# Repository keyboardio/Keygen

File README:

Setting up:

* Install perl modules
* Check out git submodule

Perl Dependencies:

JSON::XS
Moose

Non-perl Dependencies:

This tool currently builds KiCad 6.0 projects. That's not strictly necessary. If you need us to back down to 5.1, please say so.

There's a git submodule of 'kicad', which includes the keyboardio kicad footprints. Pull requests over there are welcome.

Usage:

perl layout.pl --usb=c --project=104-key --layout=kle-layouts/104.json 
cd 104-key
kicad 104-key.pro

Notes:

It currently generates schematics and layouts assuming a ATMega32U4. The schematic has sheets for three different ways to wire things up: components-on-pcb, teensy 2.0++, arduino-micro.
I know the pro micro is more popular in Japan and I'm happy to have that added as an option.
It'd just need another schematic sheet in the template project and a footprint for adding it to the pcb.
led support is a boolean option. Right now, LEDs are designed as dumb rgb pixels + an issi controller.
the logic parts of the PCB don't get placed or connected to the switch and led matrix automatically. That's a much harder wiring problem.
Instead, I hand-drew layouts for those and place them off the side of the PCB for you to drag into place and wire up.
I have produced two PCBs based on earlier versions of this tool with some manual rework. They did -work-. But results are not guaranteed.

-Jesse
jesse@keyboard.io

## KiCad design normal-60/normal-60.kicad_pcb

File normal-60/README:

A test/example of a normalish 60% generated with this tooling

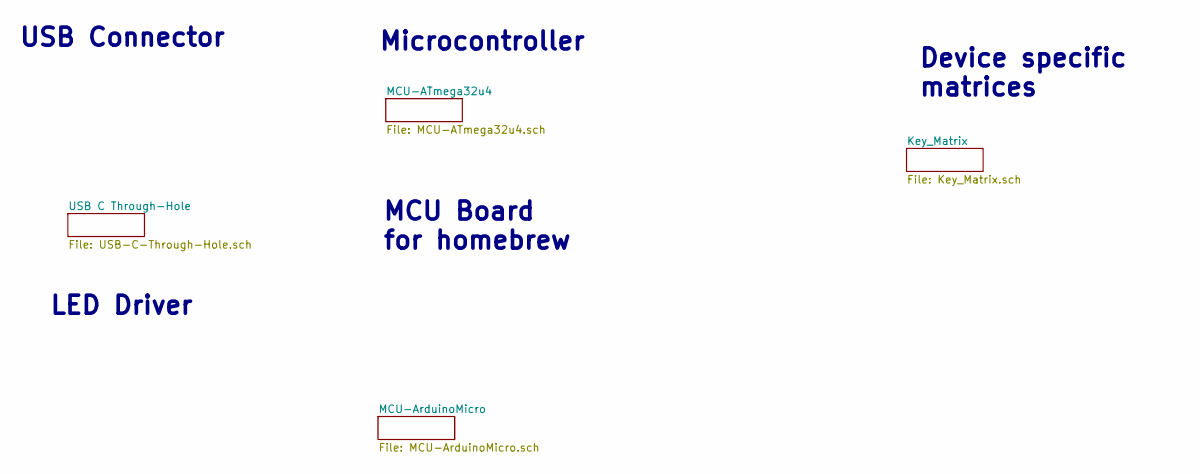
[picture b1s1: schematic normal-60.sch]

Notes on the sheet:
Device specific matrices
USB Connector
LED Driver
Microcontroller
MCU Board for homebrew

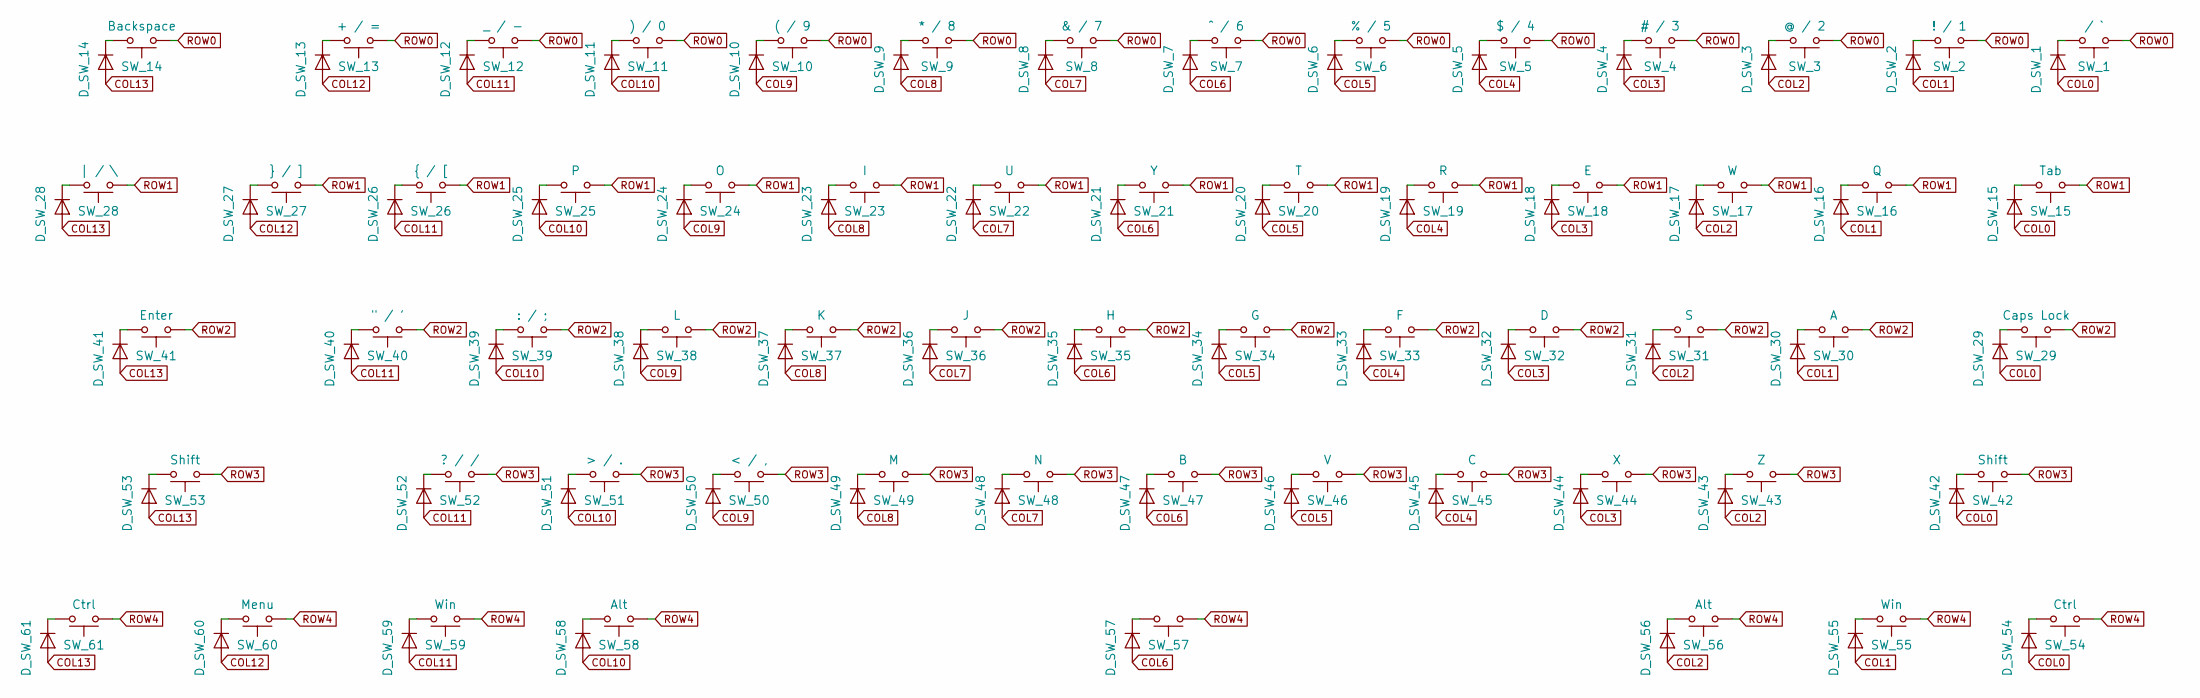
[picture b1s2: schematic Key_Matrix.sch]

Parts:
D_SW_1, D_SW_2, D_SW_3, D_SW_4, D_SW_5, D_SW_6, D_SW_7, D_SW_8, D_SW_9, D_SW_10, D_SW_11, D_SW_12, D_SW_13, D_SW_14, D_SW_15, D_SW_16, D_SW_17, D_SW_18, D_SW_19, D_SW_20, D_SW_21, D_SW_22, D_SW_23, D_SW_24, D_SW_25, D_SW_26, D_SW_27, D_SW_28, D_SW_29, D_SW_30, D_SW_31, D_SW_32, D_SW_33, D_SW_34, D_SW_35, D_SW_36, D_SW_37, D_SW_38, D_SW_39, D_SW_40, D_SW_41, D_SW_42, D_SW_43, D_SW_44, D_SW_45, D_SW_46, D_SW_47, D_SW_48, D_SW_49, D_SW_50, D_SW_51, D_SW_52, D_SW_53, D_SW_54, D_SW_55, D_SW_56, D_SW_57, D_SW_58, D_SW_59, D_SW_60, D_SW_61: 1N4148; D_SOD-123
SW_1: ~ / `; MX-KailhClip-1.00u
SW_2: ! / 1; MX-KailhClip-1.00u
SW_3: @ / 2; MX-KailhClip-1.00u
SW_4: # / 3; MX-KailhClip-1.00u
SW_5: $ / 4; MX-KailhClip-1.00u
SW_6: % / 5; MX-KailhClip-1.00u
SW_7: ^ / 6; MX-KailhClip-1.00u
SW_8: & / 7; MX-KailhClip-1.00u
SW_9: * / 8; MX-KailhClip-1.00u
SW_10: ( / 9; MX-KailhClip-1.00u
SW_11: ) / 0; MX-KailhClip-1.00u
SW_12: _ / -; MX-KailhClip-1.00u
SW_13: + / =; MX-KailhClip-1.00u
SW_14: Backspace; MX-KailhClip-1.00u
SW_15: Tab; MX-KailhClip-1.00u
SW_16: Q; MX-KailhClip-1.00u
SW_17: W; MX-KailhClip-1.00u
SW_18: E; MX-KailhClip-1.00u
SW_19: R; MX-KailhClip-1.00u
SW_20: T; MX-KailhClip-1.00u
SW_21: Y; MX-KailhClip-1.00u
SW_22: U; MX-KailhClip-1.00u
SW_23: I; MX-KailhClip-1.00u
SW_24: O; MX-KailhClip-1.00u
SW_25: P; MX-KailhClip-1.00u
SW_26: { / [; MX-KailhClip-1.00u
SW_27: } / ]; MX-KailhClip-1.00u
SW_28: | / \\; MX-KailhClip-1.00u
SW_29: Caps Lock; MX-KailhClip-1.00u
SW_30: A; MX-KailhClip-1.00u
SW_31: S; MX-KailhClip-1.00u
SW_32: D; MX-KailhClip-1.00u
SW_33: F; MX-KailhClip-1.00u
SW_34: G; MX-KailhClip-1.00u
SW_35: H; MX-KailhClip-1.00u
SW_36: J; MX-KailhClip-1.00u
SW_37: K; MX-KailhClip-1.00u
SW_38: L; MX-KailhClip-1.00u
SW_39: : / ;; MX-KailhClip-1.00u
SW_40: \" / '; MX-KailhClip-1.00u
SW_41: Enter; MX-KailhClip-1.00u
SW_42, SW_53: Shift; MX-KailhClip-1.00u
SW_43: Z; MX-KailhClip-1.00u
SW_44: X; MX-KailhClip-1.00u
SW_45: C; MX-KailhClip-1.00u
SW_46: V; MX-KailhClip-1.00u
SW_47: B; MX-KailhClip-1.00u
SW_48: N; MX-KailhClip-1.00u
SW_49: M; MX-KailhClip-1.00u
SW_50: < / ,; MX-KailhClip-1.00u
SW_51: > / .; MX-KailhClip-1.00u
SW_52: ? / /; MX-KailhClip-1.00u
SW_54, SW_61: Ctrl; MX-KailhClip-1.00u
SW_55, SW_59: Win; MX-KailhClip-1.00u
SW_56, SW_58: Alt; MX-KailhClip-1.00u
SW_57: MX-KailhClip-1.00u
SW_60: Menu; MX-KailhClip-1.00u

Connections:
COL0: D_SW_1.2 (A), D_SW_15.2 (A), D_SW_29.2 (A), D_SW_42.2 (A), D_SW_54.2 (A); also elsewhere on the board
COL1: D_SW_2.2 (A), D_SW_16.2 (A), D_SW_30.2 (A), D_SW_55.2 (A); also elsewhere on the board
COL2: D_SW_3.2 (A), D_SW_17.2 (A), D_SW_31.2 (A), D_SW_43.2 (A), D_SW_56.2 (A); also elsewhere on the board
COL3: D_SW_4.2 (A), D_SW_18.2 (A), D_SW_32.2 (A), D_SW_44.2 (A); also elsewhere on the board
COL4: D_SW_5.2 (A), D_SW_19.2 (A), D_SW_33.2 (A), D_SW_45.2 (A); also elsewhere on the board
COL5: D_SW_6.2 (A), D_SW_20.2 (A), D_SW_34.2 (A), D_SW_46.2 (A); also elsewhere on the board
COL6: D_SW_7.2 (A), D_SW_21.2 (A), D_SW_35.2 (A), D_SW_47.2 (A), D_SW_57.2 (A); also elsewhere on the board
COL7: D_SW_8.2 (A), D_SW_22.2 (A), D_SW_36.2 (A), D_SW_48.2 (A); also elsewhere on the board
COL8: D_SW_9.2 (A), D_SW_23.2 (A), D_SW_37.2 (A), D_SW_49.2 (A); also elsewhere on the board
COL9: D_SW_10.2 (A), D_SW_24.2 (A), D_SW_38.2 (A), D_SW_50.2 (A); also elsewhere on the board
COL10: D_SW_11.2 (A), D_SW_25.2 (A), D_SW_39.2 (A), D_SW_51.2 (A), D_SW_58.2 (A); also elsewhere on the board
COL11: D_SW_12.2 (A), D_SW_26.2 (A), D_SW_40.2 (A), D_SW_52.2 (A), D_SW_59.2 (A); also elsewhere on the board
COL12: D_SW_13.2 (A), D_SW_27.2 (A), D_SW_60.2 (A); also elsewhere on the board
COL13: D_SW_14.2 (A), D_SW_28.2 (A), D_SW_41.2 (A), D_SW_53.2 (A), D_SW_61.2 (A); also elsewhere on the board
unnamed: D_SW_1.1 (K), SW_1.2
unnamed: D_SW_2.1 (K), SW_2.2
unnamed: D_SW_3.1 (K), SW_3.2
unnamed: D_SW_4.1 (K), SW_4.2
unnamed: D_SW_5.1 (K), SW_5.2
unnamed: D_SW_6.1 (K), SW_6.2
unnamed: D_SW_7.1 (K), SW_7.2
unnamed: D_SW_8.1 (K), SW_8.2
unnamed: D_SW_9.1 (K), SW_9.2
unnamed: D_SW_10.1 (K), SW_10.2
unnamed: D_SW_11.1 (K), SW_11.2
unnamed: D_SW_12.1 (K), SW_12.2
unnamed: D_SW_13.1 (K), SW_13.2
unnamed: D_SW_14.1 (K), SW_14.2
unnamed: D_SW_15.1 (K), SW_15.2
unnamed: D_SW_16.1 (K), SW_16.2
unnamed: D_SW_17.1 (K), SW_17.2
unnamed: D_SW_18.1 (K), SW_18.2
unnamed: D_SW_19.1 (K), SW_19.2
unnamed: D_SW_20.1 (K), SW_20.2
unnamed: D_SW_21.1 (K), SW_21.2
unnamed: D_SW_22.1 (K), SW_22.2
unnamed: D_SW_23.1 (K), SW_23.2
unnamed: D_SW_24.1 (K), SW_24.2
unnamed: D_SW_25.1 (K), SW_25.2
unnamed: D_SW_26.1 (K), SW_26.2
unnamed: D_SW_27.1 (K), SW_27.2
unnamed: D_SW_28.1 (K), SW_28.2
unnamed: D_SW_29.1 (K), SW_29.2
unnamed: D_SW_30.1 (K), SW_30.2
unnamed: D_SW_31.1 (K), SW_31.2
unnamed: D_SW_32.1 (K), SW_32.2
unnamed: D_SW_33.1 (K), SW_33.2
unnamed: D_SW_34.1 (K), SW_34.2
unnamed: D_SW_35.1 (K), SW_35.2
unnamed: D_SW_36.1 (K), SW_36.2
unnamed: D_SW_37.1 (K), SW_37.2
unnamed: D_SW_38.1 (K), SW_38.2
unnamed: D_SW_39.1 (K), SW_39.2
unnamed: D_SW_40.1 (K), SW_40.2
unnamed: D_SW_41.1 (K), SW_41.2
unnamed: D_SW_42.1 (K), SW_42.2
unnamed: D_SW_43.1 (K), SW_43.2
unnamed: D_SW_44.1 (K), SW_44.2
unnamed: D_SW_45.1 (K), SW_45.2
unnamed: D_SW_46.1 (K), SW_46.2
unnamed: D_SW_47.1 (K), SW_47.2
unnamed: D_SW_48.1 (K), SW_48.2
unnamed: D_SW_49.1 (K), SW_49.2
unnamed: D_SW_50.1 (K), SW_50.2
unnamed: D_SW_51.1 (K), SW_51.2
unnamed: D_SW_52.1 (K), SW_52.2
unnamed: D_SW_53.1 (K), SW_53.2
unnamed: D_SW_54.1 (K), SW_54.2
unnamed: D_SW_55.1 (K), SW_55.2
unnamed: D_SW_56.1 (K), SW_56.2
unnamed: D_SW_57.1 (K), SW_57.2
unnamed: D_SW_58.1 (K), SW_58.2
unnamed: D_SW_59.1 (K), SW_59.2
unnamed: D_SW_60.1 (K), SW_60.2
unnamed: D_SW_61.1 (K), SW_61.2
ROW0: SW_1.1, SW_2.1, SW_3.1, SW_4.1, SW_5.1, SW_6.1, SW_7.1, SW_8.1, SW_9.1, SW_10.1, SW_11.1, SW_12.1, SW_13.1, SW_14.1; also elsewhere on the board
ROW1: SW_15.1, SW_16.1, SW_17.1, SW_18.1, SW_19.1, SW_20.1, SW_21.1, SW_22.1, SW_23.1, SW_24.1, SW_25.1, SW_26.1, SW_27.1, SW_28.1; also elsewhere on the board
ROW2: SW_29.1, SW_30.1, SW_31.1, SW_32.1, SW_33.1, SW_34.1, SW_35.1, SW_36.1, SW_37.1, SW_38.1, SW_39.1, SW_40.1, SW_41.1; also elsewhere on the board
ROW3: SW_42.1, SW_43.1, SW_44.1, SW_45.1, SW_46.1, SW_47.1, SW_48.1, SW_49.1, SW_50.1, SW_51.1, SW_52.1, SW_53.1; also elsewhere on the board
ROW4: SW_54.1, SW_55.1, SW_56.1, SW_57.1, SW_58.1, SW_59.1, SW_60.1, SW_61.1; also elsewhere on the board

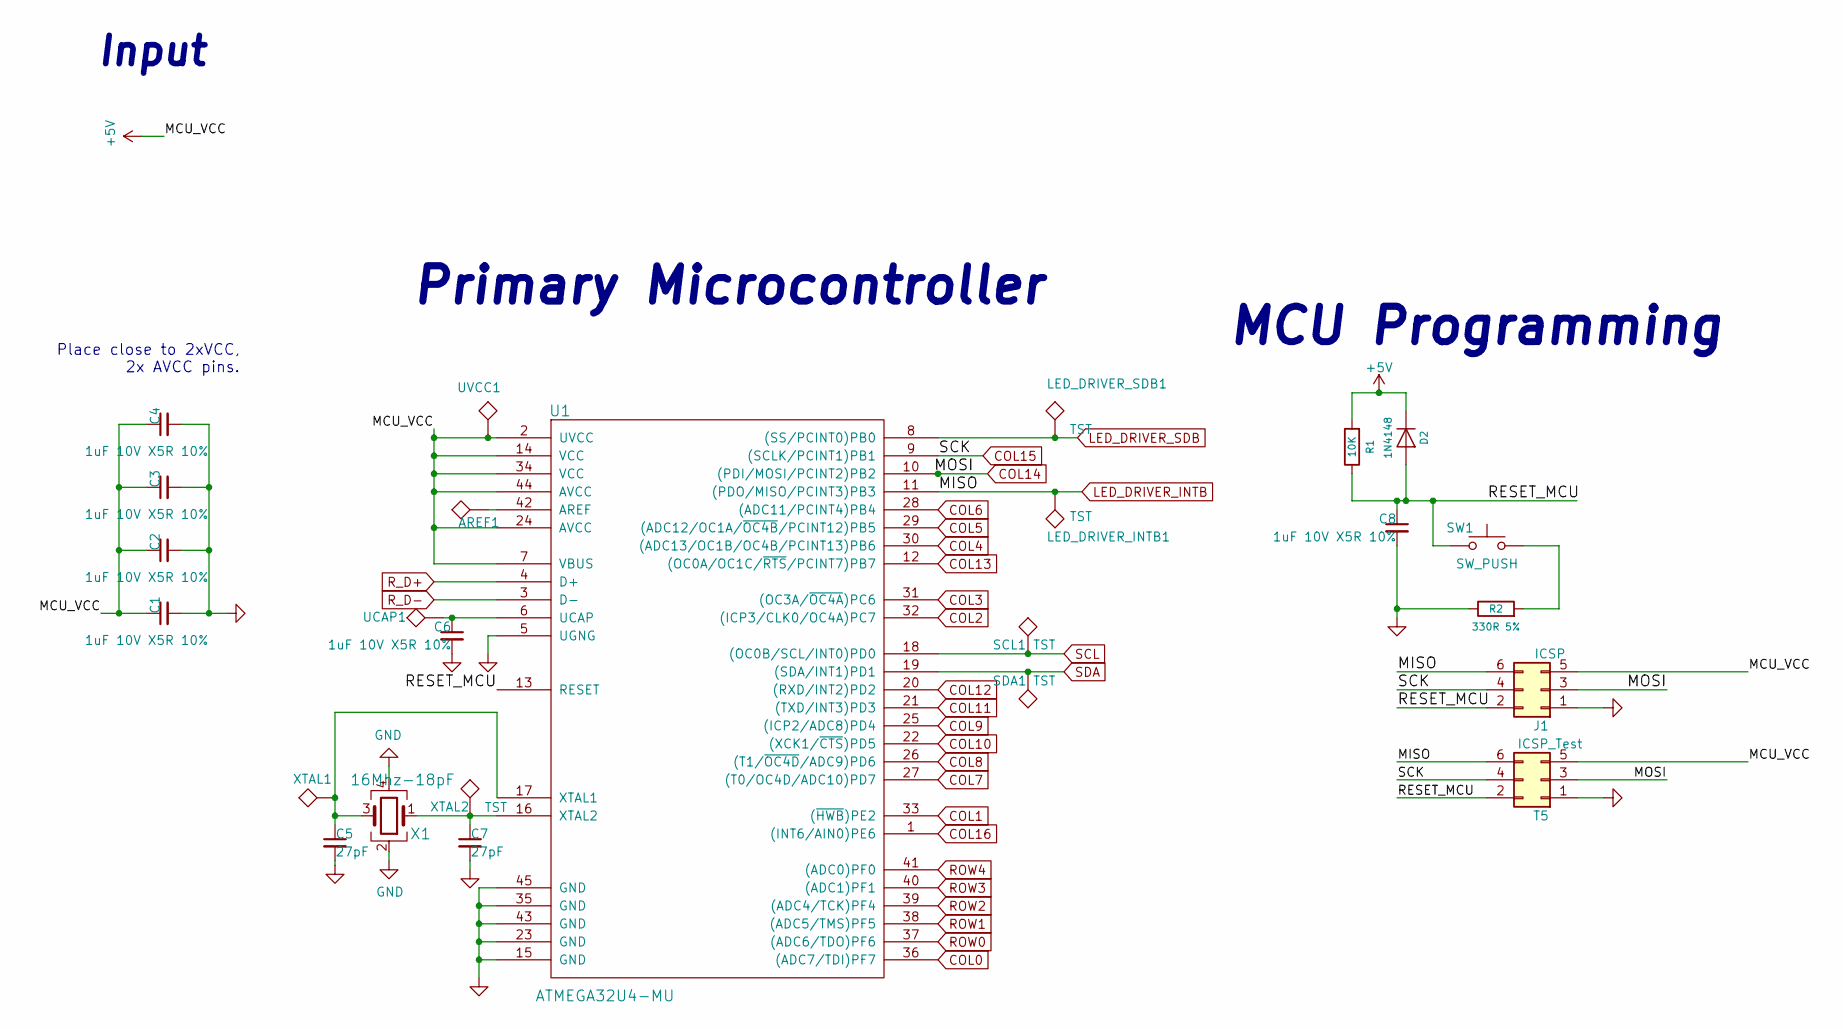
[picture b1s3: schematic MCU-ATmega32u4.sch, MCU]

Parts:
AREF1: TST; TestPoint_Pad_D1.5mm
C1, C2, C3, C4, C6, C8: 1uF 10V X5R 10%; C_0603_1608Metric; MPN CC0603KRX5R6BB105; DigiKey 311-1443-2-ND
C5, C7: 27pF; C_0603_1608Metric; MPN CC0603JRNPO9BN270; DigiKey 311-1063-1-ND
D2: 1N4148; D_SOD-123; MPN 1N4148W-7-F; DigiKey 1N4148W-FDITR-ND
J1: ICSP; Model_01_ICSP_cutout_pins; MPN M20-8760342; DigiKey 952-1922-ND
LED_DRIVER_INTB1: TST; TestPoint_Pad_D1.5mm
LED_DRIVER_SDB1: TST; TestPoint_Pad_D1.5mm
R1: 10K; R_0603_1608Metric; MPN RR0816P-103-D; DigiKey RR08P10.0KDTR-ND
R2: 330R 5%; R_0603_1608Metric; MPN 311-330GRTR-ND; DigiKey 311-330GRTR-ND
SCL1: TST; TestPoint_Pad_D1.5mm
SDA1: TST; TestPoint_Pad_D1.5mm
SW1: SW_PUSH; SW_SPST_TL3342; MPN TL3342F160QG/TR; DigiKey EG2531TR-ND
T5: ICSP_Test; Six_Pin_Test_Point
U1: ATMEGA32U4-MU; QFN-44-1EP_7x7mm_P0.5mm_EP5.15x5.15mm_ThermalVias; MPN ATMEGA32U4-MU; DigiKey ATMEGA32U4-MU-ND
UCAP1: TST; TestPoint_Pad_D1.5mm
UVCC1: TST; TestPoint_Pad_D1.5mm
X1: 16Mhz-18pF; Crystal_SMD_SeikoEpson_TSX3225-4Pin_3.2x2.5mm; MPN X1E000021069600; DigiKey TSX-322516.0000MF20G-C-ND
XTAL1, XTAL2: TST; TestPoint_Pad_D1.5mm

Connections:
+5V: C1.1, C2.1, C3.1, C4.1, D2.1 (K), J1.5, R1.2, T5.5, U1.2 (UVCC), U1.7 (VBUS), U1.14 (VCC), U1.24 (AVCC), U1.34 (VCC), U1.44 (AVCC), UVCC1.1; also elsewhere on the board
/MCU-ATmega32u4/RESET_MCU: C8.1, D2.2 (A), J1.2, R1.1, SW1.2, T5.2, U1.13 (RESET)
COL0: U1.36 ((ADC7/TDI)PF7); also elsewhere on the board
COL1: U1.33 ((~HWB~)PE2); also elsewhere on the board
COL2: U1.32 ((ICP3/CLK0/OC4A)PC7); also elsewhere on the board
COL3: U1.31 ((OC3A/~OC4A~)PC6); also elsewhere on the board
COL4: U1.30 ((ADC13/OC1B/OC4B/PCINT13)PB6); also elsewhere on the board
COL5: U1.29 ((ADC12/OC1A/~OC4B~/PCINT12)PB5); also elsewhere on the board
COL6: U1.28 ((ADC11/PCINT4)PB4); also elsewhere on the board
COL7: U1.27 ((T0/OC4D/ADC10)PD7); also elsewhere on the board
COL8: U1.26 ((T1/~OC4D~/ADC9)PD6); also elsewhere on the board
COL9: U1.25 ((ICP2/ADC8)PD4); also elsewhere on the board
COL10: U1.22 ((XCK1/~CTS~)PD5); also elsewhere on the board
COL11: U1.21 ((TXD/INT3)PD3); also elsewhere on the board
COL12: U1.20 ((RXD/INT2)PD2); also elsewhere on the board
COL13: U1.12 ((OC0A/OC1C/~RTS~/PCINT7)PB7); also elsewhere on the board
COL14: J1.3, T5.3, U1.10 ((PDI/MOSI/PCINT2)PB2)
COL15: J1.4, T5.4, U1.9 ((SCLK/PCINT1)PB1)
COL16: U1.1 ((INT6/AIN0)PE6)
LED_DRIVER_INTB: J1.6, LED_DRIVER_INTB1.1, T5.6, U1.11 ((PDO/MISO/PCINT3)PB3)
LED_DRIVER_SDB: LED_DRIVER_SDB1.1, U1.8 ((SS/PCINT0)PB0)
unnamed: AREF1.1, U1.42 (AREF)
unnamed: C5.1, U1.17 (XTAL1), X1.3, XTAL1.1
unnamed: C6.1, U1.6 (UCAP), UCAP1.1
unnamed: C7.1, U1.16 (XTAL2), X1.1, XTAL2.1
unnamed: R2.2, SW1.1
ROW0: U1.37 ((ADC6/TDO)PF6); also elsewhere on the board
ROW1: U1.38 ((ADC5/TMS)PF5); also elsewhere on the board
ROW2: U1.39 ((ADC4/TCK)PF4); also elsewhere on the board
ROW3: U1.40 ((ADC1)PF1); also elsewhere on the board
ROW4: U1.41 ((ADC0)PF0); also elsewhere on the board
R_D+: U1.4 (D+); also elsewhere on the board
R_D-: U1.3 (D-); also elsewhere on the board
SCL: SCL1.1, U1.18 ((OC0B/SCL/INT0)PD0)
SDA: SDA1.1, U1.19 ((SDA/INT1)PD1)

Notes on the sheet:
MCU Programming
Primary Microcontroller
Place close to 2xVCC, 2x AVCC pins.
Input

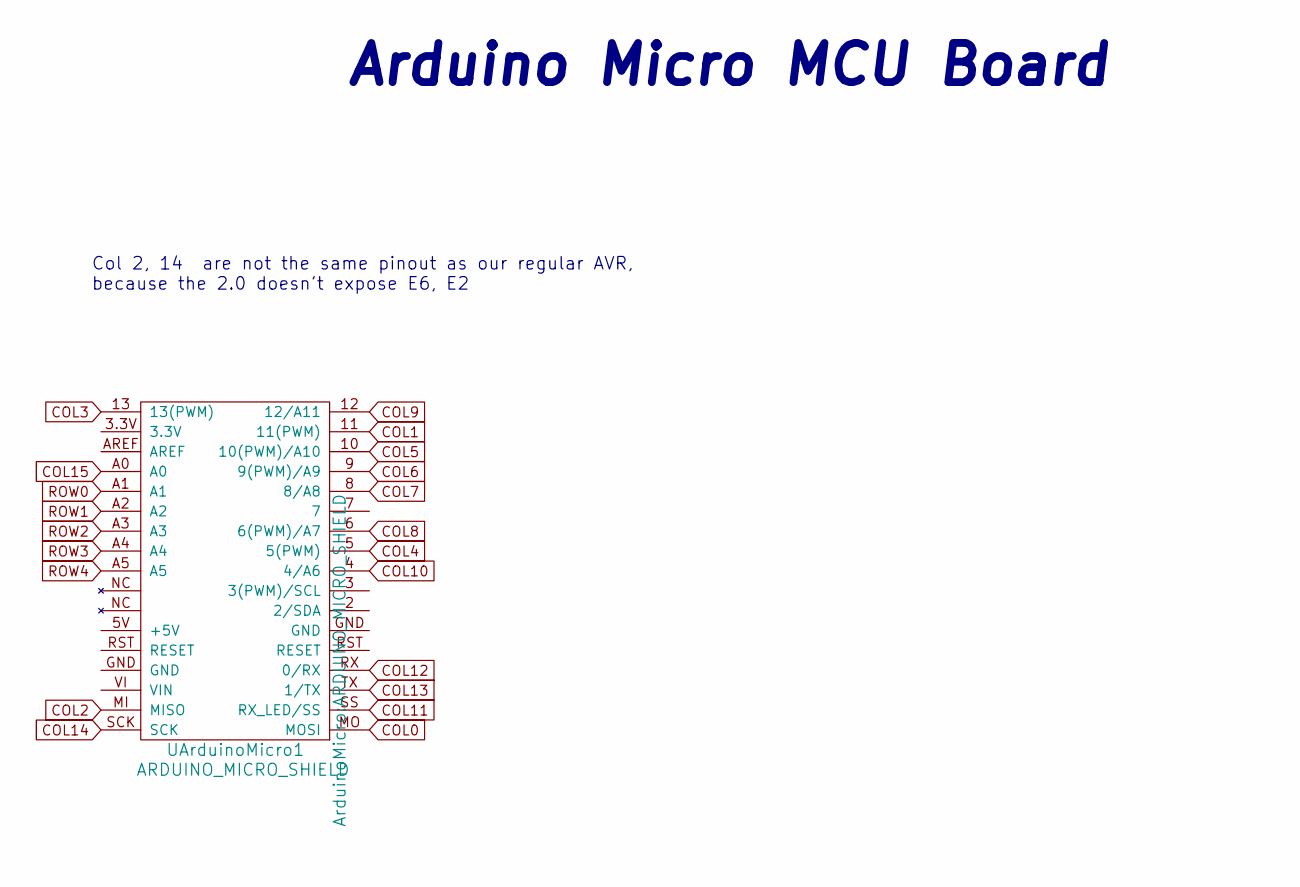
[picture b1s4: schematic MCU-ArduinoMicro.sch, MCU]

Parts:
UArduinoMicro1: ARDUINO_MICRO_SHIELD

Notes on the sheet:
Arduino Micro MCU Board
Col 2, 14 are not the same pinout as our regular AVR, because the 2.0 doesn't expose E6, E2

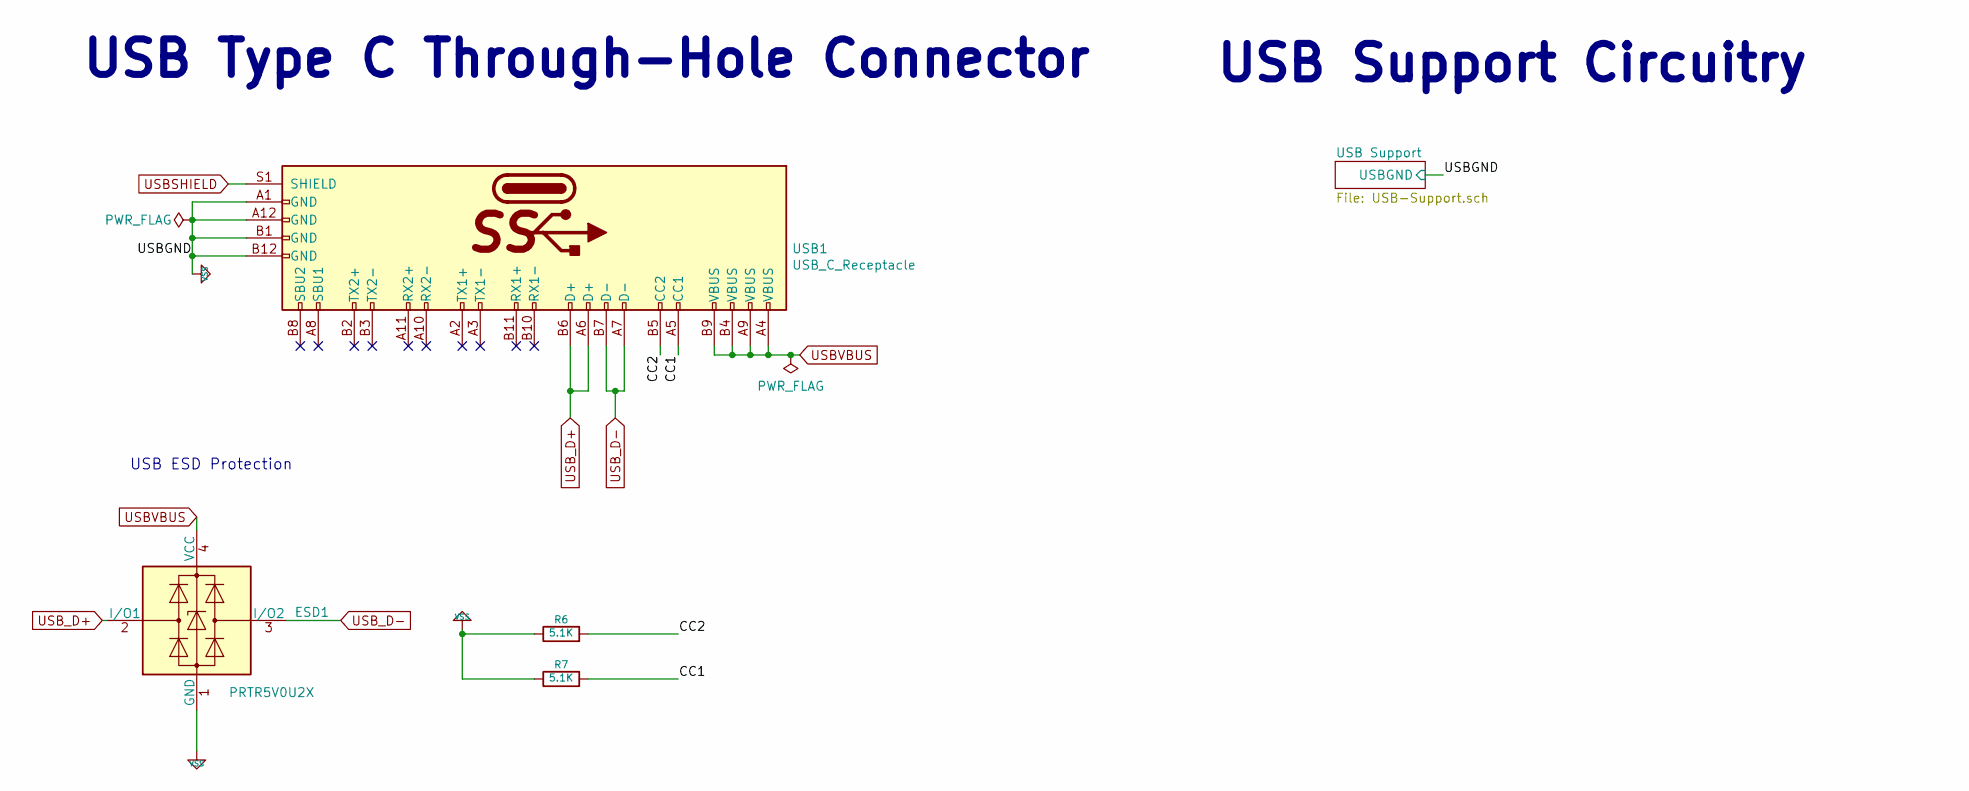
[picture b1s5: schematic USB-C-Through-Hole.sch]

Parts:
ESD1: PRTR5V0U2X; MPN PRTR5V0U2X; DigiKey 1727-3884-2-ND
R6: 5.1K; R_0603_1608Metric; MPN RT0603BRD075K1L; DigiKey RR08P5.1KDTR-ND
R7: 5.1K; R_0603_1608Metric; MPN RT0603BRD075K1L; LCSC C122969
USB1: USB_C_Receptacle; USB_C_Receptacle_GCT_USB4085; MPN GCT_USB4085

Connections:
/USB C Through-Hole/CC1: R7.2, USB1.A5 (CC1)
/USB C Through-Hole/CC2: R6.2, USB1.B5 (CC2)
USBSHIELD: USB1.S1 (SHIELD); also elsewhere on the board
USBVBUS: ESD1.4 (VCC), USB1.A4 (VBUS), USB1.A9 (VBUS), USB1.B4 (VBUS), USB1.B9 (VBUS); also elsewhere on the board
USB_D+: ESD1.2 (I/O1), USB1.A6 (D+), USB1.B6 (D+); also elsewhere on the board
USB_D-: ESD1.3 (I/O2), USB1.A7 (D-), USB1.B7 (D-); also elsewhere on the board

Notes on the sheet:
USB Type C Through-Hole Connector
USB Support Circuitry
USB ESD Protection

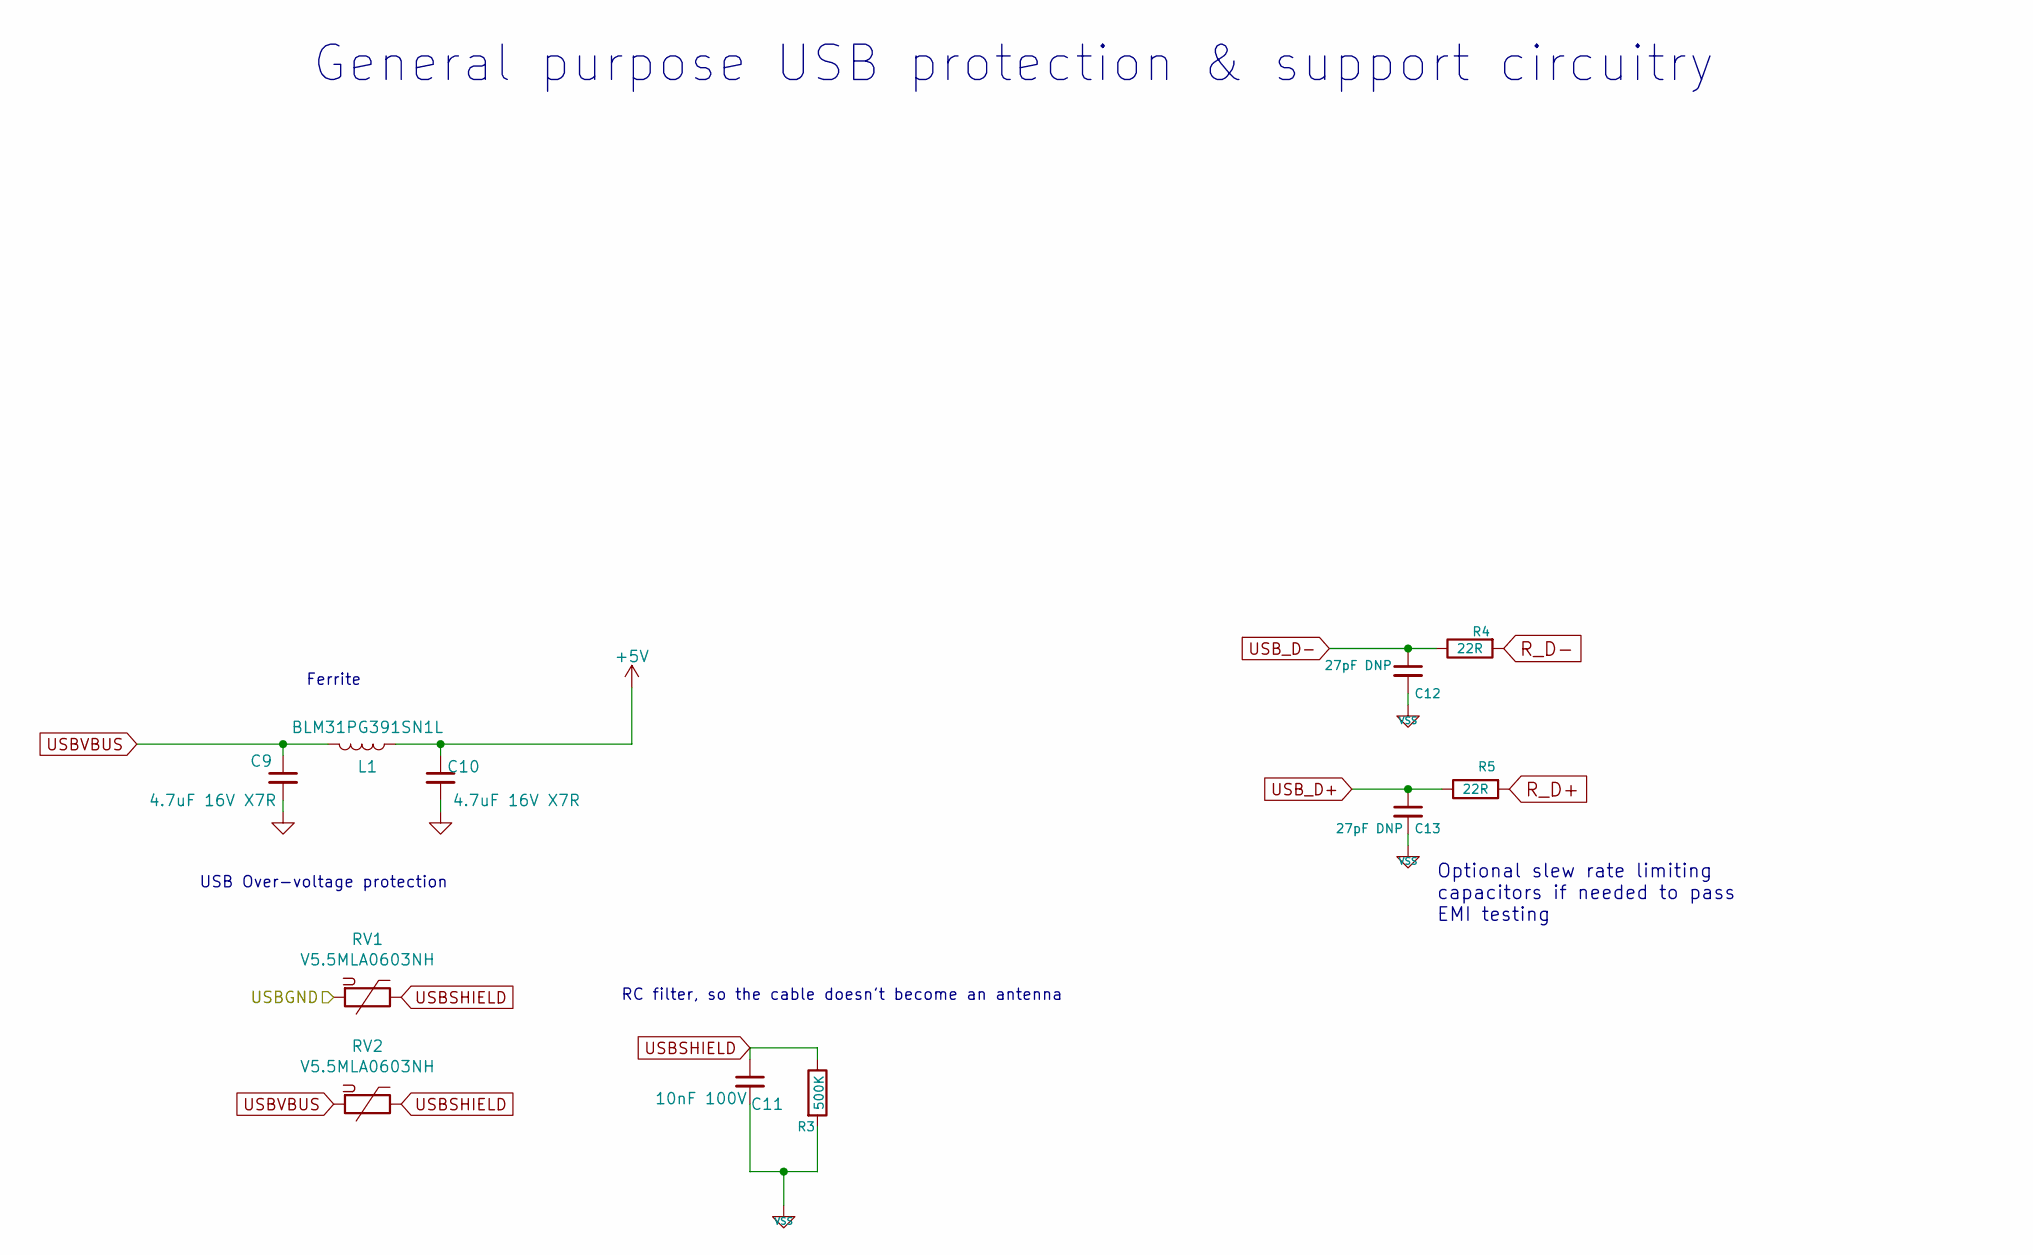
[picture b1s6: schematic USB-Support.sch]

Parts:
C9, C10: 4.7uF 16V X7R; C_0805_2012Metric; MPN CC0805KKX7R7BB475; DigiKey 311-1883-2-ND
C11: 10nF 100V; C_0805_2012Metric; MPN CC0805KRX7R0BB103; DigiKey 311-1475-1-ND
C12, C13: 27pF DNP; C_0603_1608Metric; MPN CC0603JRNPO9BN270; DigiKey 311-1063-1-ND
L1: BLM31PG391SN1L; R_1206_3216Metric; MPN BLM31PG391SN1L; DigiKey 490-5229-2-ND
R3: 500K; R_0603_1608Metric; MPN RC0603FR-07499KL; DigiKey 311-499KHRTR-ND
R4, R5: 22R; R_0603_1608Metric; MPN RC0603FR-0722RL; DigiKey 311-22.0HRTR-ND
RV1, RV2: V5.5MLA0603NH; R_0603_1608Metric; MPN V5.5MLA0603NH; DigiKey F3363CT-ND

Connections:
+5V: C10.1, L1.1; also elsewhere on the board
R_D+: R5.2; also elsewhere on the board
R_D-: R4.2; also elsewhere on the board
USBSHIELD: C11.1, R3.1, RV1.1, RV2.1; also elsewhere on the board
USBVBUS: C9.1, L1.2, RV2.2; also elsewhere on the board
USB_D+: C13.1, R5.1; also elsewhere on the board
USB_D-: C12.1, R4.1; also elsewhere on the board

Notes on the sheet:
Optional slew rate limiting capacitors if needed to pass EMI testing
Ferrite
USB Over-voltage protection
RC filter, so the cable doesn't become an antenna
General purpose USB protection & support circuitry

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
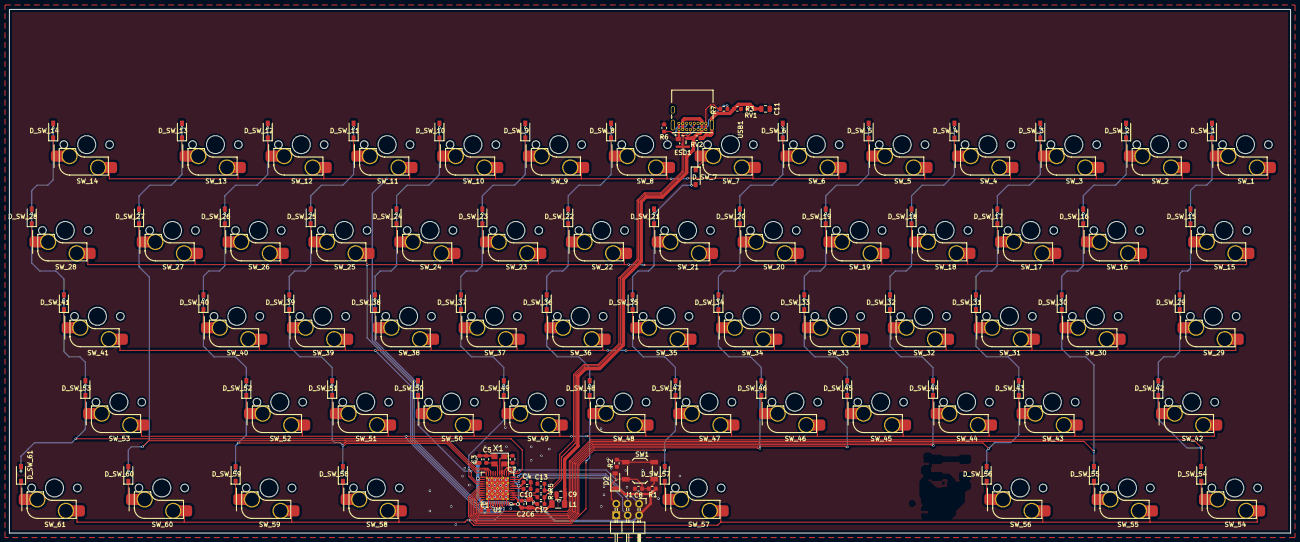
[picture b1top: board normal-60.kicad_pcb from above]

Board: 2 copper layers, 284.3 x 116.2 mm, 152 parts (0 on the bottom side), 98 nets.

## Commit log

2019-09-29 check in a version of the keyboard generator without keyboardio's secret projects
2019-09-30 remove debugging statements
2019-09-30 README
2019-09-30 added some notes I sent to @nameless911 by twitter
2019-10-02 Add a new USB C variant: the GCT USB4085, which is entirely through-hole
2019-10-02 perltidy layout.pl
2019-10-02 Starting to add schematic support for the through-hole USB C connector
2019-10-02 .gitignore
2019-10-02 update to add USB C through-hole connector
2019-10-02 conditionally include our arduino micro socket
2019-10-02 make it possible to specify a parent output directory
2019-10-02 fix a bug in our schematic item removal
2019-10-05 doc c-through-hole
2019-10-06 working on adding support for jlcpcb small batch assembly
2019-10-06 starting to add support for alternate mcus
    first as a configurable -layout- of the 32u4
2019-10-06 starting to add the layouts for the -mu
2019-10-06 It appears that kicad tried to renumber some of our parts
2019-10-06 undo some of the dumb autonumbering
2019-10-10 Trying to get back to Kicad 5.1 compat and fix USB routing
2019-10-12 added a couple more sample layouts
2019-10-13 Added an example of a 60% routed with this tooling
2019-10-14 make it work with 5.1 again
2020-08-18 snapshot changes
2021-12-10 Check in build-spacecadet

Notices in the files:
parts and their libraries:
Copyright 2016 Accelerated Designs. All rights reserved.
